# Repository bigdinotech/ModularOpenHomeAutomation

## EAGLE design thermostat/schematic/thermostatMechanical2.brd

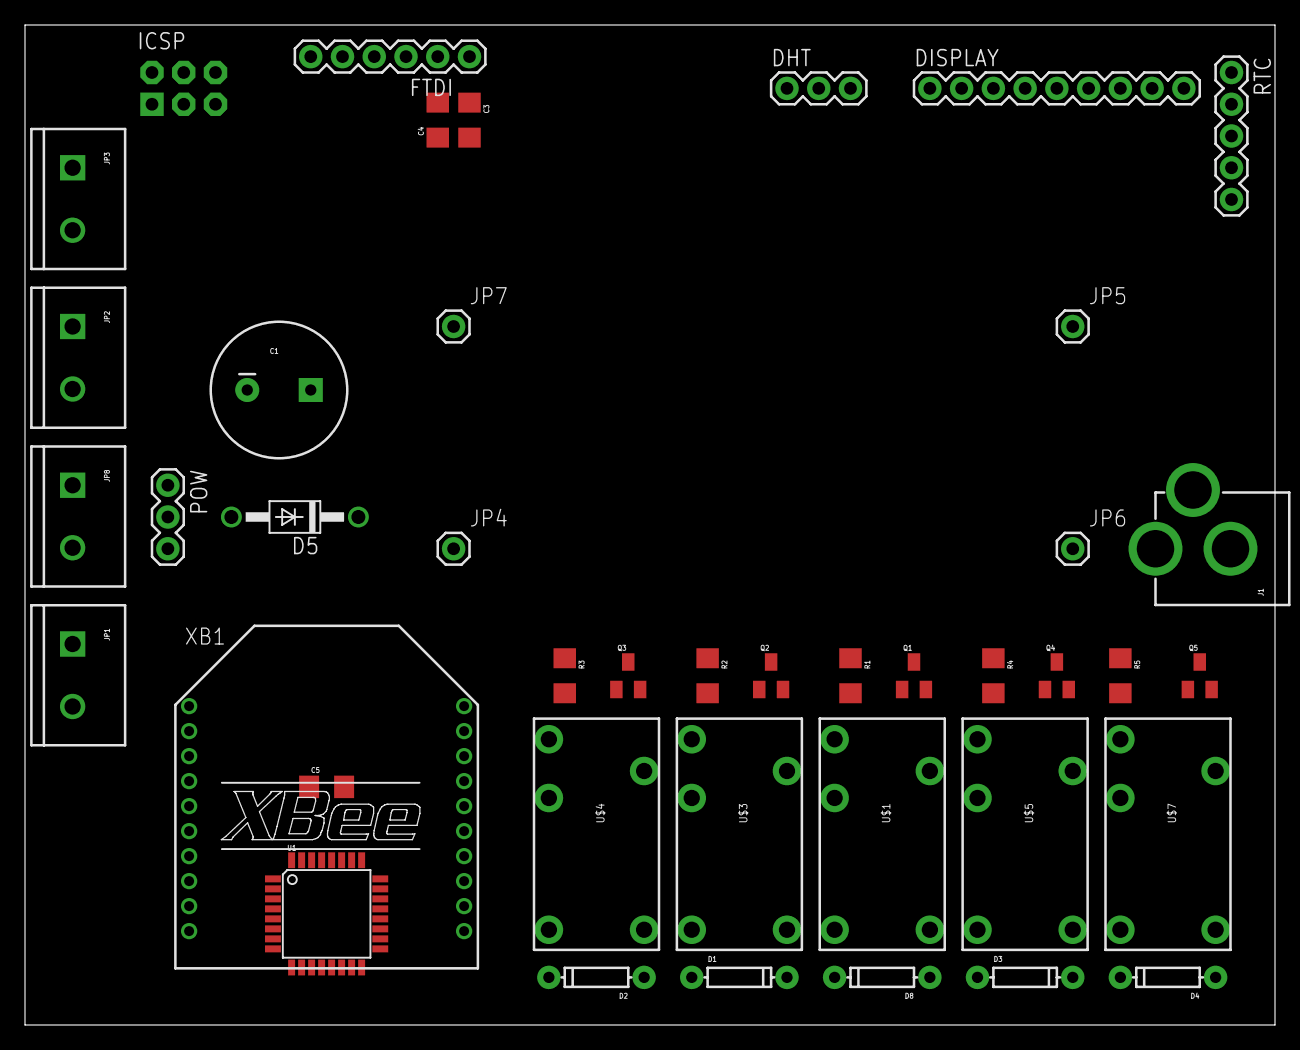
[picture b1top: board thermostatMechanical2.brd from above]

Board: 2 copper layers, 100.0 x 80.0 mm, 42 parts (0 on the bottom side), 38 nets, no tracks yet.

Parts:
C1: CAP-09538; CPOL-RADIAL-1000UF-25V
C3: 1206
C4, C5: 1.0uF; 1206
D1, D2, D3, D4, D8: DIODE-1N4148
D5: 1N4004; DO41-10
DHT: 1X03
DISPLAY: M09; 1X09
FTDI: FTDI_BASIC
ICSP: 2X3-NS
J1: POWER_JACKPTH; POWER_JACK_PTH
JP1, JP2, JP3, JP8: M025MM; SCREWTERMINAL-5MM-2
JP4, JP5, JP6, JP7: M01PTH; 1X01
POW: 1X03
Q1, Q2, Q3, Q4, Q5: SOT23
R1, R2, R3, R4, R5: 1206
RTC: 1X05
U1: ATMEGA168; TQFP32-08
U$1, U$3, U$4, U$5, U$7: RELAYPTH4; RELAY-JZC
XB1: XBEE

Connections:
3.3V: C5.1, DHT.2, DISPLAY.8, FTDI.VCC, U1.4, U1.6, U1.18, U1.20, XB1.1
5V: C4.1, D1.C, D2.C, D3.C, D4.C, D8.C, ICSP.2, J1.PWR, JP7.1, RTC.4, U$1.5, U$3.5, U$4.5, U$5.5, U$7.5
35V: C1.+, D5.C, JP4.1
D1_SELECT: DISPLAY.4, U1.14
D2_SELECT: DISPLAY.3, U1.12
DHT_SIG: DHT.1, U1.2
DISPLAY_PWM: DISPLAY.2, U1.13
GND: C1.-, C4.2, C5.2, DHT.3, DISPLAY.9, FTDI.CTS, FTDI.GND, ICSP.6, J1.GND, J1.GNDBREAK, JP1.1, JP5.1, JP6.1, Q1.2, Q2.2, Q3.2, Q4.2, Q5.2, RTC.5, U1.3, U1.5, U1.21, XB1.10
G_FAN: JP1.2, U1.9, U$4.4
MISO: DISPLAY.6, ICSP.1, U1.16
MOSI: DISPLAY.5, ICSP.4, U1.15
unnamed: Q2.1, R2.2
unnamed: Q3.1, R3.2
unnamed: D8.A, Q1.3, U$1.1
unnamed: D1.A, Q2.3, U$3.1
unnamed: D2.A, Q3.3, U$4.1
unnamed: Q4.1, R4.2
unnamed: D3.A, Q4.3, U$5.1
unnamed: Q1.1, R1.2
unnamed: Q5.1, R5.2
unnamed: D4.A, Q5.3, U$7.1
unnamed: C3.1, FTDI.DTR
RC: JP8.2, POW.3
RH: JP8.1, POW.1
RST: C3.2, ICSP.5
RXD: U1.30, XB1.2
SCK: DISPLAY.7, ICSP.3, U1.17
SD_SELECT: DISPLAY.1, U1.11
TXD: U1.31, XB1.3
VAC_IN: D5.A, POW.2, U$1.3, U$3.3, U$4.3, U$5.3, U$7.3
W1_CTRL: R1.1, U1.25
W1_HEAT: JP3.1, U$1.4
W2_CTRL: R4.1, U1.26
W2_HEAT: JP3.2, U$5.4
Y1_COOL: JP2.1, U$3.4
Y1_CTRL: R2.1, U1.23
Y2_COOL: JP2.2, U$7.4
Y2_CTRL: R5.1, U1.24

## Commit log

2014-12-12 Initial Commit
    Initial Commit
2014-12-12 Cleanup of thermostat module
    Cleanup of thermostat module
2014-12-19 Bug Fix #1
    homeAuto.html update for thermostat commands
    fixed transmit data bug on homeAutomation sketch
    update thermostat module to use new commands
2014-12-19 Garage Module Update
    Update Garage Module to use SMP protocol
2014-12-19 Home Automation Sketch Cleanup
    Remove misleading debug messages
2015-07-16 Added CSS styles
    Initial implementation of CSS styling

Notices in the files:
parts and their libraries:
SparkFun-Capacitors: Licensing: Creative Commons ShareAlike 4.0 International - https://creativecommons.org/licenses/by-sa/4.0
